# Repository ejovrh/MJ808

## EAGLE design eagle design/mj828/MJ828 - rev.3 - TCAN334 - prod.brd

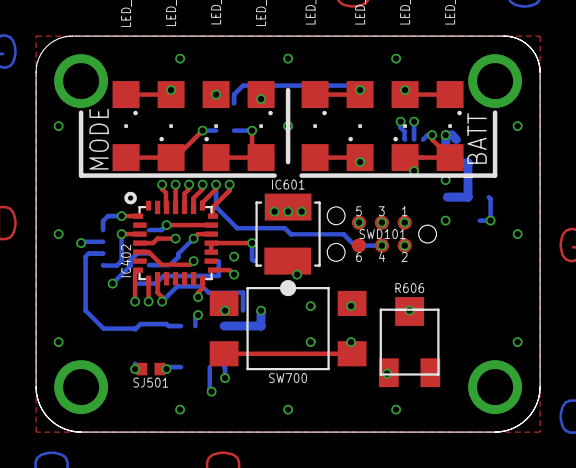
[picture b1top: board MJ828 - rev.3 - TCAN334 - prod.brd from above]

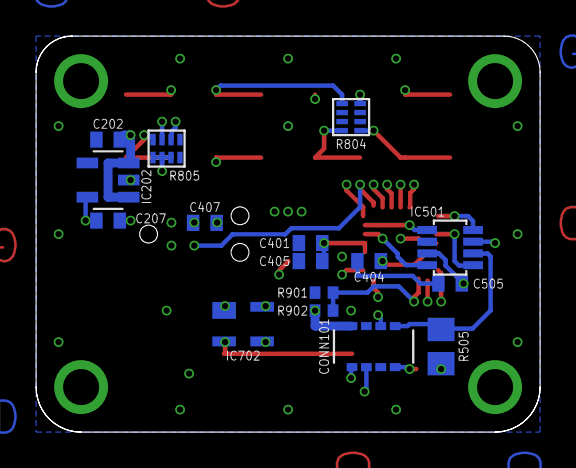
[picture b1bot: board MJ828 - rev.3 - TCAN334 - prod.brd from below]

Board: 4 copper layers, 28.0 x 22.0 mm, 30 parts (16 on the bottom side), 28 nets.

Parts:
C202: 1μF / 10V; C0402
C207: 1μF; C0402
C401, C405, C407: 0.1u; C0402
C404: 1u; C0402
C505: 0.1μF; C0402
CONN101: 104250-0820; SMD
IC202: LDK320AM33R; SOT-23-5L
IC402: STM32F042G6U6; UFQFPN-28
IC501: TCAN334; SOT23-8
IC601: SFH 320 FA-Z; P-LCC-2
IC702: MAX6816EUS+T; 4SOT143
LED_BATT801, LED_BATT802, LED_BATT803, LED_BATT804: 156120BS82500; SML1206
LED_BLUE800: 156120BS82500; SML1206
LED_GREEN800: 156120VS82500; SML1206
LED_RED800: 156120RS82500; SML1206
LED_YELLOW800: 156120YS82500; SML1206
R505: 120; R0805
R606: 3313J-1-104E - 100k; 3313
R804: 741X083151JP / 150Ω; 0402
R805: 741X083101JP / 100Ω; 0402
R901, R902: 100k; R0402
SJ501: CAN termination; R0402
SW700: TL3305CF160QG; SMD
SWD101: TC2030-NL

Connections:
3V3: C207.2, C401.2, C404.2, C405.2, C505.1, CONN101.P$7, IC202.OUT, IC402.5_VDDA, IC402.17_VDD, IC402.18_VDDIO2, IC501.P$3, IC702.4_VCC, R606.2_WIPER, SWD101.1_TVCC
!SHDN!: IC402.3_PF1, IC501.P$5
!STBY!: IC402.1_PB8, IC501.P$8
BAT+: C202.1, CONN101.P$5, IC202.EN, IC202.IN, R902.2
BREAK_IN: CONN101.P$4, IC402.8_PA2
CAN_H: CONN101.P$1, IC501.P$7, SJ501.2
CAN_INFRA:CAN_JMPR: R505.2, SJ501.1
CAN_L: CONN101.P$8, IC501.P$6, R505.1
CAN_RX: IC402.19_PA9-[PA11], IC501.P$4
CAN_TX: IC402.20_PA10-[PA12], IC501.P$1
CP1: IC402.26_PB5, LED_BATT803.A, LED_BATT804.C, LED_GREEN800.A, LED_RED800.C
CP2: IC402.24_PB3, LED_BLUE800.A, LED_YELLOW800.C, R804.8
CP3: IC402.25_PB4, LED_BATT801.C, LED_BATT802.A, R804.2
CP4: IC402.23_PA15, R805.2, R805.4, R805.6
GND: C202.2, C207.1, C401.1, C404.1, C405.1, C407.1, C505.2, CONN101.P$2, IC202.GND, IC402.16_VSS, IC501.P$2, IC601.EMITTER, IC702.1_GND, R901.1, SW700.3, SW700.4, SWD101.5_GND
HIGH_IN: CONN101.P$3, IC402.7_PA1
LED:D_BATT1&2: LED_BATT801.A, LED_BATT802.C, R805.3
LED:D_BATT3&4: LED_BATT803.C, LED_BATT804.A, R805.1
LED:D_BLUE: LED_BLUE800.C, R805.5
LED:D_RED&GREEN: LED_GREEN800.C, LED_RED800.A, R804.7
LED:D_YELLOW: LED_YELLOW800.A, R804.1
PHOTOTRANSISTOR: IC402.15_PB1, IC601.COLLECTOR, R606.3_CW
PUSHBUTTON:SWITCH_IN: IC702.2_IN, SW700.1, SW700.2
SWITCH: IC402.14_PB0, IC702.3_OUT
SYS_NRST: C407.2, IC402.4_NRST, SWD101.3_T_NRST
SYS_SWCLK: IC402.22_PA14, SWD101.4_T_SWCLK
SYS_SWDIO: IC402.21_PA13, SWD101.2_T_SWDIO
VBAT+: IC402.9_PA3, R901.2, R902.1

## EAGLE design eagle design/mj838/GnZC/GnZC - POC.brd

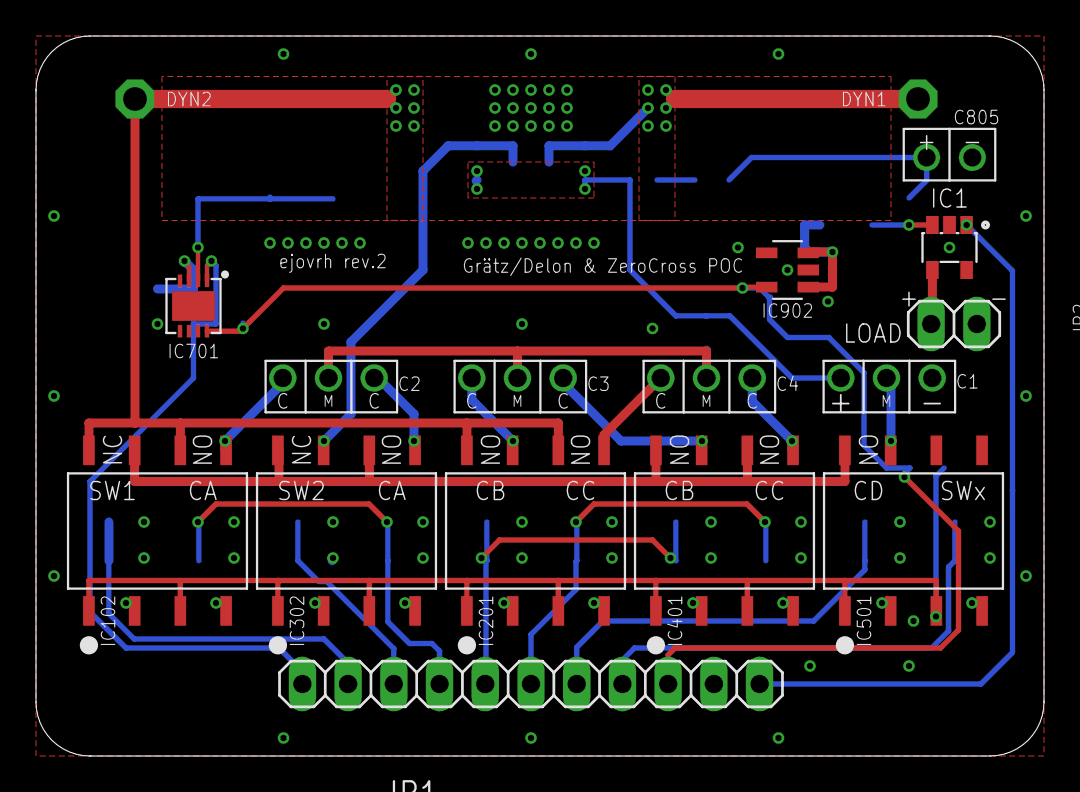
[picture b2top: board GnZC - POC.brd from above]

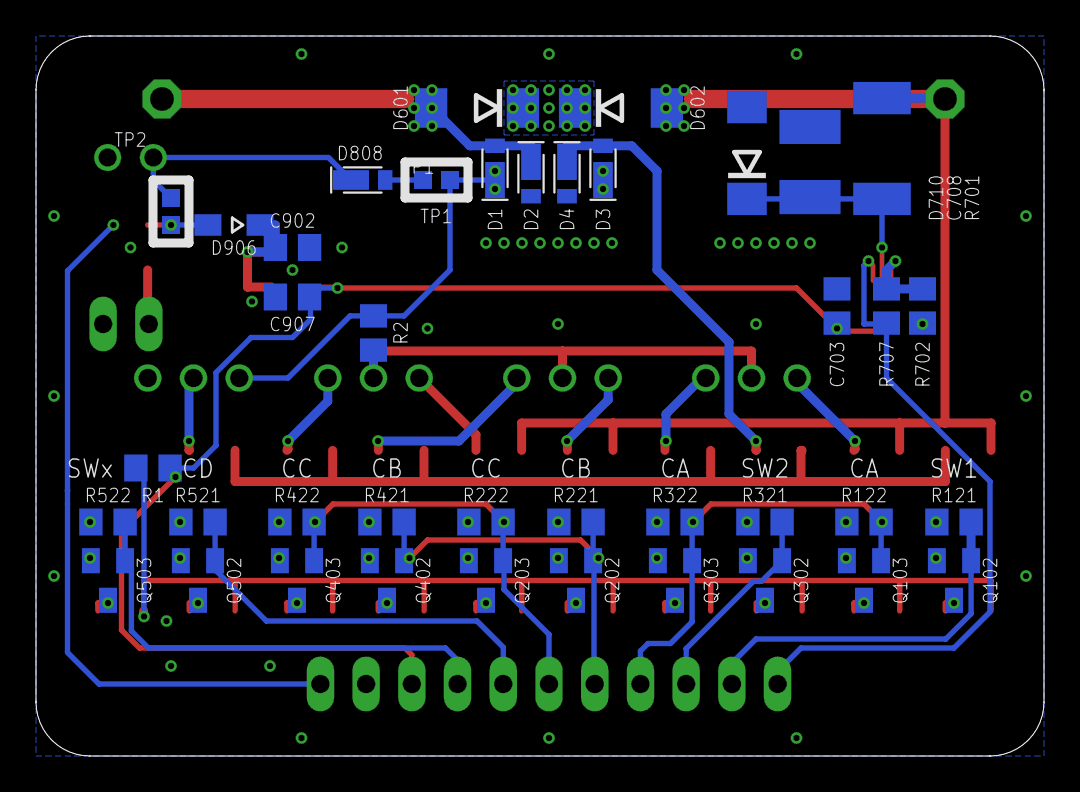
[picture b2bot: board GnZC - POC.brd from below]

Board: 2 copper layers, 56.0 x 40.0 mm, 59 parts (42 on the bottom side), 43 nets.

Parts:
C1: 330μF / 35V / ultralow ESR; TH-2S
C2, C3, C4: 1500μF / 35V / ultralow ESR; TH-2S-BACK-TO-BACK
C703: 0.1uF / 10V; C0805
C708: 10nF / 100v; C1812
C805: 2P 4700μF / 35V / ultralow ESR; TH
C902, C907: 1uF / 10V; C0805
D1, D2, D3, D4, D808: CUHS20S30,H3F; US2H
D601, D602: 19V/5W; DO214AA
D710: 6V/3W; DO214AA
D906: BAT 60A E6327; SOD323-W
IC1: MIC2514YM5; SOT-23-5
IC102, IC302: LBA710S; SMD_DIP8
IC201, IC401, IC501: LAA710S; SMD_DIP8
IC701: LT1638IDD#PBF; DFN-8
IC902: LDK320AM33R; SOT-23-5L
JP1: out; 1X11
JP2: 2.54-pinhead; 1X02
Q102, Q103, Q202, Q203, Q302, Q303, Q402, Q403, Q502, Q503: IRLML2402TRPBF; SOT23
R1: 430R/0.5W; R0805
R2: 47k; R0805
R121, R122, R221, R222, R321, R322, R421, R422, R521, R522, R702, R707: 10k; R0805
R701: 10k/3W; R2512
TP2: dynamo 1; P1-13
TP3: dynamo 2; P1-13
TP4: TP1l; TP10SQ
TP5: TP1r; TP10SQ
TP6: TP2l; TP10SQ
TP7: TP2r; TP10SQ

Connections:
3V3: C703.2, C907.2, IC701.8_V+, IC902.OUT, JP1.9, R1.2
3V3:LDK_IN: C902.1, D906.C, IC902.EN, IC902.IN
CAA: C2.1_C, IC102.5_DRAIN2-1
CAB: C2.3_C, IC302.5_DRAIN2-1
CBA: C3.1_C, IC201.7_DRAIN1-1
CBB: C3.3_C, IC401.7_DRAIN1-1
CCA: C4.1_C, IC201.5_DRAIN2-1
CCB: C4.3_C, IC401.5_DRAIN2-1
DYNAMO1: D1.C, D2.A, D601.A, TP2.TP
DYNAMO2_AFTER_TUNING-CAP_SW: IC102.7_DRAIN1-1, IC302.6_DRAIN2-2, IC302.8_DRAIN1-2, IC401.6_DRAIN2-2, IC401.8_DRAIN1-2, IC501.8_DRAIN1-2
DYNAMO2_BEFORE_TUNING-CAP_SW: D602.A, IC102.6_DRAIN2-2, IC102.8_DRAIN1-2, IC201.6_DRAIN2-2, IC201.8_DRAIN1-2, R701.1, TP3.TP
DYNAMO2_DELON: C1.2_MID, IC501.7_DRAIN1-1
DYNAMO2_GRAETZ: D3.C, D4.A, IC302.7_DRAIN1-1
GND: C1.3_NEG, C703.1, C708.1, C805.NEG, C902.2, C907.1, D2.C, D4.C, D710.A, IC1.P$2, IC701.4_V-, IC701.9_V-, IC902.GND, JP1.10, JP2.2, Q102.2, Q103.2, Q202.2, Q203.2, Q302.2, Q303.2, Q402.2, Q403.2, Q502.2, Q503.2, R121.2, R122.2, R221.2, R222.2, R321.2, R322.2, R421.2, R422.2, R521.2, R522.2, R702.1
LOAD_HIGHSIDE: IC1.P$4, JP2.1
LOAD_SWITCH: IC1.P$1, JP1.11
OVP:ZENER_COMMON: D601.C, D602.C
SSR_ANODE: IC102.1_ANODE1, IC102.3_ANODE2, IC201.1_ANODE1, IC201.3_ANODE2, IC302.1_ANODE1, IC302.3_ANODE2, IC401.1_ANODE1, IC401.3_ANODE2, IC501.1_ANODE1, IC501.3_ANODE2, R1.1
SSR_NC/NO1:SW1_CAT: IC102.2_CATHODE1, Q102.3
SSR_NC/NO1:SW2_CAT: IC102.4_CATHODE2, Q103.3
SSR_NC/NO2:SW1_CAT: IC302.2_CATHODE1, Q302.3
SSR_NC/NO2:SW2_CAT: IC302.4_CATHODE2, Q303.3
SSR_NO/NO1:SW1_CAT: IC201.2_CATHODE1, Q202.3
SSR_NO/NO1:SW2_CAT: IC201.4_CATHODE2, Q203.3
SSR_NO/NO2:SW1_CAT: IC401.2_CATHODE1, Q402.3
SSR_NO/NO2:SW2_CAT: IC401.4_CATHODE2, Q403.3
SSR_NO/NO3:SW1_CAT: IC501.2_CATHODE1, Q502.3
SSR_NO/NO3:SW2_CAT: IC501.4_CATHODE2, Q503.3
SW1_CTRL: JP1.2, Q102.1, R121.1
SW2_CTRL: JP1.3, Q302.1, R321.1
SW_CA_CTRL: JP1.4, Q103.1, Q303.1, R122.1, R322.1
SW_CB_CTRL: JP1.5, Q202.1, Q402.1, R221.1, R421.1
SW_CC_CTRL: JP1.6, Q203.1, Q403.1, R222.1, R422.1
SW_CD_CTRL: JP1.7, Q502.1, R521.1
SW_X_CTRL: JP1.8, Q503.1, R522.1
TUNING_CAP_BIAS: C2.2_MID, C3.2_MID, C4.2_MID, R2.1
V_RECT_TP1-IN: C1.1_POS, D1.A, D3.A, R2.2, TP4.TP
V_RECT_TP1-OUT: D808.C, TP5.TP
V_REGULATED_TP2-IN: C805.POS, D808.A, TP6.TP
V_REGULATED_TP2-OUT: D906.A, IC1.P$3, TP7.TP
ZERO-CROSS_DETECTOR:N$6: C708.2, D710.C, IC701.2_A_IN-, R701.2
ZERO-CROSS_DETECTOR:N$12: IC701.3_A_IN+, R702.2, R707.2
ZEROCROSS: IC701.1_A_OUT, JP1.1, R707.1

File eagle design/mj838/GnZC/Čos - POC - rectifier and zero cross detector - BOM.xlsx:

Qty | Value | Device | Package | Parts | mouser part no. | mouser url
1 | 0.1u | C-EUC0805 | C0805 | C703 | 80-C1812C104JDR | https://hr.mouser.com/ProductDetail/80-C1812C104JDR
12 | 10k | R-EU_R0805 | R0805 | R121 R122 R221 R222 R321 R322 R421 R422 R521 R522 R702 R707
1 | 10k/3W | R-EU_R2512 | R2512 | R701 | 652-CHP2512JW103ELF | https://hr.mouser.com/ProductDetail/652-CHP2512JW103ELF
1 | 10n/100v | C-EUC1812 | C1812 | C708 | 77-VJ1812Y103JXEAT | https://hr.mouser.com/ProductDetail/77-VJ1812Y103JXEAT
2 | 19V/5W | ZENER-DIODEDO214AA | DO214AA | D601 D602 | 833-SMBJ5356B-TP | https://hr.mouser.com/ProductDetail/833-SMBJ5356B-TP
2 | 1u / 10V | C-EUC0805 | C0805 | C902 C907 | 581-08051C105K4T2A | https://hr.mouser.com/ProductDetail/581-08051C105K4T2A
1 | 430R/0.5W | R-EU_R0805 | R0805 | R1 | 667-ERJ-P06F4300V | https://hr.mouser.com/ProductDetail/667-ERJ-P06F4300V
1 | 47k | R-EU_R0805 | R0805 | R2
1 | 6V/3W | ZENER-DIODEDO214AA | DO214AA | D710 | 494-SMBJ5340BE3/TR13 | https://hr.mouser.com/ProductDetail/494-SMBJ5340BE3-TR13
5 | CUHS20S30 H3F | CUHS20S30 | US2H | D1 D2 D3 D4 D808 | 757-CUHS20S30H3F | https://hr.mouser.com/ProductDetail/Toshiba/CUHS20S30H3F?qs=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
10 | IRLML2402TRPBF | MOSFET-NREFLOW | SOT23 | Q102 Q103 Q202 Q203 Q302 Q303 Q402 Q403 Q502 Q503 | 942-IRLML2402TRPBF | https://hr.mouser.com/ProductDetail/942-IRLML2402TRPBF
3 | LAA710S | LAA710 | SMD_DIP8 | IC201 IC401 IC501 | 849-LAA710S | https://hr.mouser.com/ProductDetail/849-LAA710S
2 | LBA710S | LBA710 | SMD_DIP8 | IC102 IC302 | 849-LBA710S | https://hr.mouser.com/ProductDetail/849-LBA710S
1 | LDK320AM33R | LDK320SOT-23-5L | SOT-23-5L | IC902 | 511-LDK320AM33R | https://hr.mouser.com/ProductDetail/511-LDK320AM33R
1 | LT1638IDD#PBF | LT1638 | DFN-8 | IC701 | 584-LT1638IDD#PBF | https://hr.mouser.com/ProductDetail/584-LT1638IDD%23PBF

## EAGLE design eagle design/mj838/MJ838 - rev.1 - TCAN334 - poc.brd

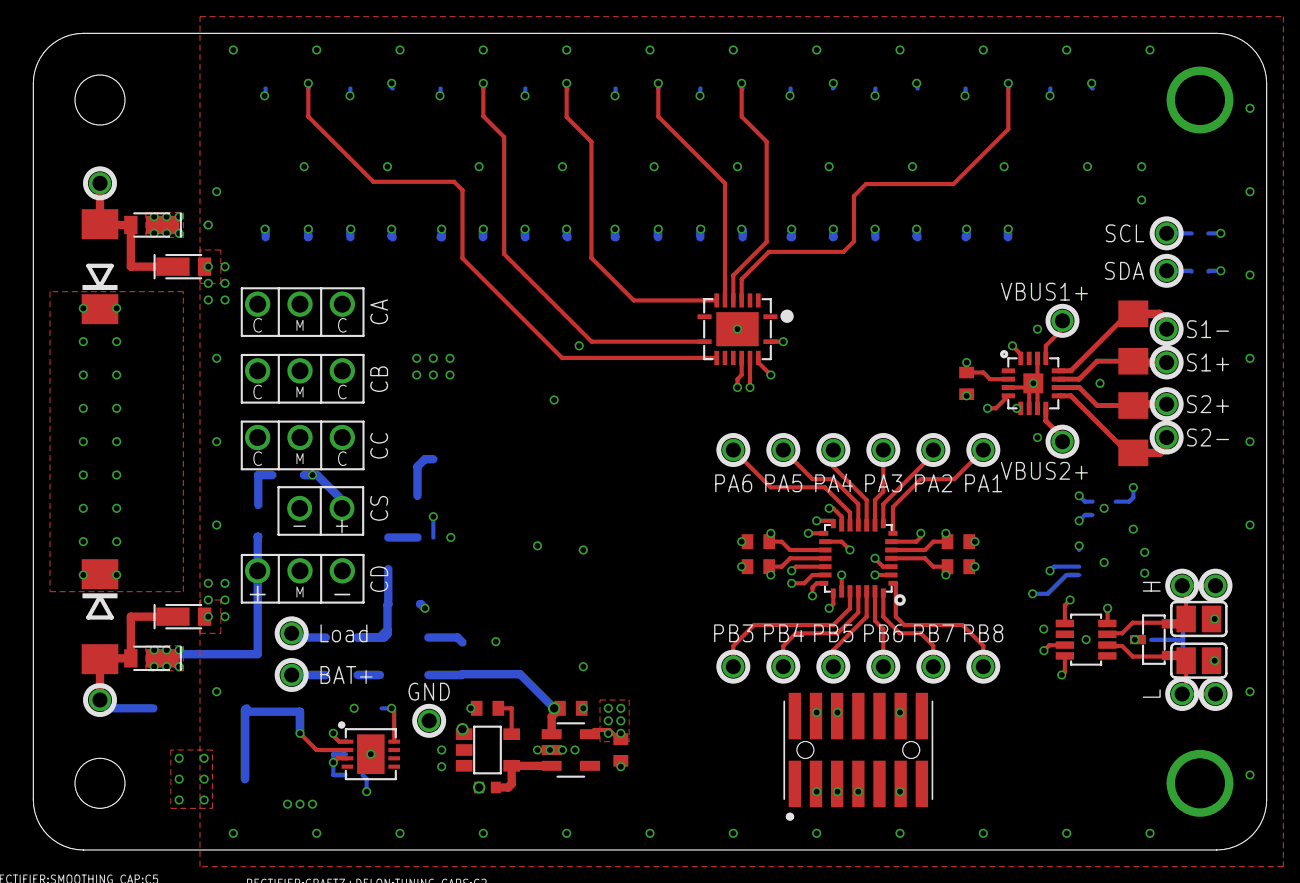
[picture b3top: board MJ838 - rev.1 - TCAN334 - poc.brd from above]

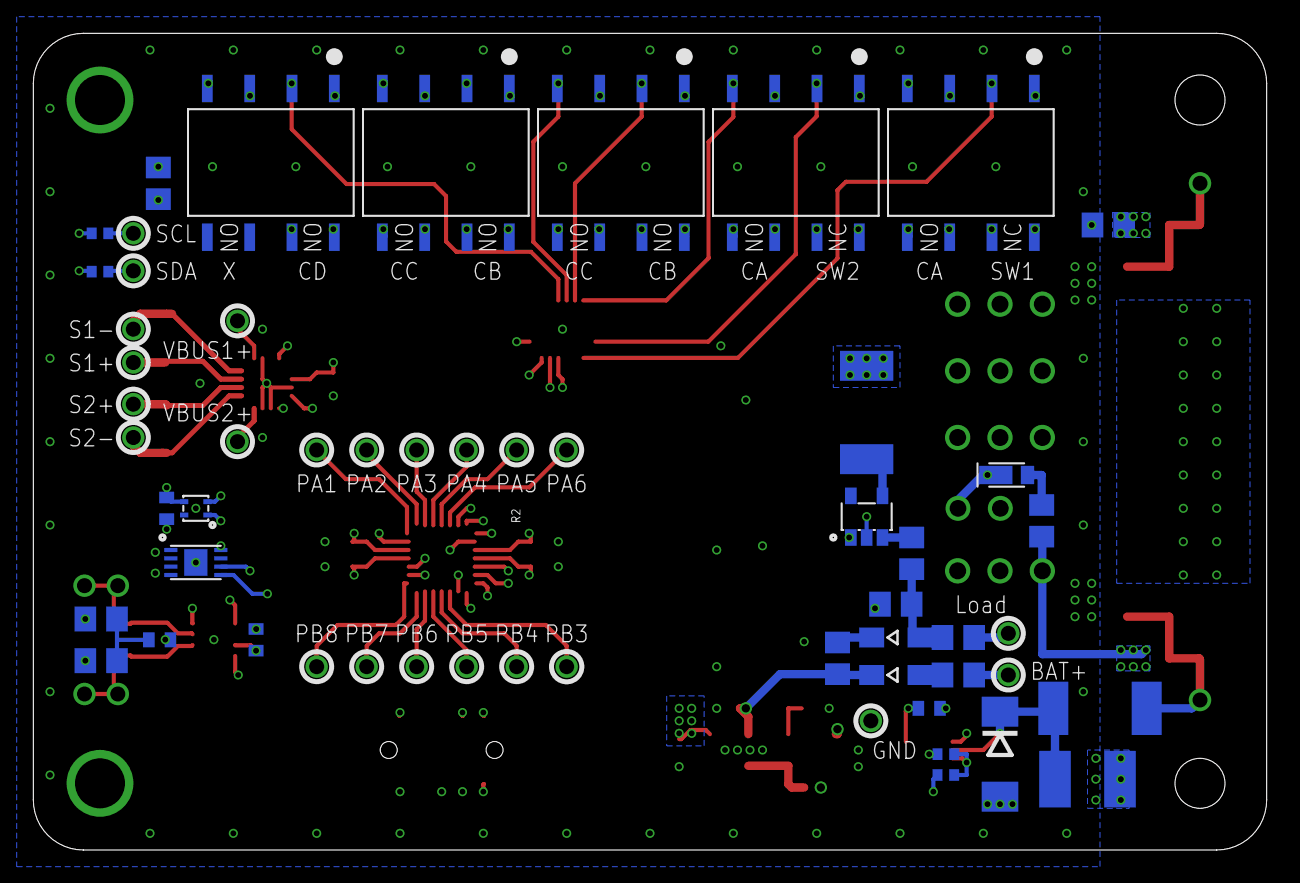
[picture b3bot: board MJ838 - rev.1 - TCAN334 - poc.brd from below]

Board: 6 copper layers, 74.0 x 49.0 mm, 95 parts (33 on the bottom side), 71 nets.

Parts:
C301, C305, C307, C405, C605, C905: 0.1uF / 10V; C0402
C304: 1uF / 10V; C0402
C401: 47nF / 10V; C0402
D501, D502: BAT 60A E6327; SOD323-W
IC302: STM32F042G6U6; UFQFPN-28
IC401: TCAN334GDCNT; SOT23-8
IC402: SZNUP2105LT1G; SOT-23-3
IC601: PAC1952T-1E/4MX; VQFN16
IC701: MB85RC16PN-G-AMERE1; SON-8
IC801: MIC2514YM5; SOT-23-5
IC901: SHT40-AD1F-R2; SMD
J1: FTSH-107-01-L-DV-K-A; FTSH10701LDVKA
R1, R2, R3, R502, R504, R505: 0R; R0805
R4, R5: 4k7; R0402
R401, R402: 60R, 0.5W; R0805
R601, R602: 0.1R / 0.5W / 0.25%; R1206
R802: 12R / 5W; R2512
RECTIFIER:3V3:C1, RECTIFIER:3V3:C2, RECTIFIER:3V3:C7: 1uF / 10V; C0402
RECTIFIER:3V3:IC1: R3119N058A; SOT23-5
RECTIFIER:3V3:IC2: LDK320AM33R; SOT-23-5L
RECTIFIER:3V3:R1: 100k / 0.1W; R0402
RECTIFIER:GRAETZ+DELON:D1, RECTIFIER:GRAETZ+DELON:D2, RECTIFIER:GRAETZ+DELON:D3, RECTIFIER:GRAETZ+DELON:D4: CUHS20S30,H3F; US2H
RECTIFIER:GRAETZ+DELON:DELON:C1: 330μF / 35V / ultralow ESR; TH-2S
RECTIFIER:GRAETZ+DELON:DELON:SSR_NO/NO3:IC1: LAA710S; SMD_DIP8
RECTIFIER:GRAETZ+DELON:IC1: TLC59208FIRGYR; VQFN16
RECTIFIER:GRAETZ+DELON:R1: 430R/0.5W; R0805
RECTIFIER:GRAETZ+DELON:TUNING_CAPS:C2, RECTIFIER:GRAETZ+DELON:TUNING_CAPS:C3, RECTIFIER:GRAETZ+DELON:TUNING_CAPS:C4: 1500μF / 35V / ultralow ESR; TH-2S-BACK-TO-BACK
RECTIFIER:GRAETZ+DELON:TUNING_CAPS:R2: 47k; R0805
RECTIFIER:GRAETZ+DELON:TUNING_CAPS:SSR_NC/NO1:IC2, RECTIFIER:GRAETZ+DELON:TUNING_CAPS:SSR_NC/NO2:IC2: LBA710S; SMD_DIP8
RECTIFIER:GRAETZ+DELON:TUNING_CAPS:SSR_NO/NO1:IC1, RECTIFIER:GRAETZ+DELON:TUNING_CAPS:SSR_NO/NO2:IC1: LAA710S; SMD_DIP8
RECTIFIER:OVP:D1, RECTIFIER:OVP:D2: 19V/5W; DO214AA
RECTIFIER:SMOOTHING_CAP:C5: 2P 4700μF / 35V / ultralow ESR; TH
RECTIFIER:SMOOTHING_CAP:D8: CUHS20S30,H3F; US2H
RECTIFIER:ZERO-CROSS_DETECTOR:C3: 0.1uF / 10V; C0402
RECTIFIER:ZERO-CROSS_DETECTOR:C8: 10nF / 100v; C1812
RECTIFIER:ZERO-CROSS_DETECTOR:D10: 6V/3W; DO214AA
RECTIFIER:ZERO-CROSS_DETECTOR:IC1: LT1638IDD#PBF; DFN-8
RECTIFIER:ZERO-CROSS_DETECTOR:R1: 10k/3W; R2512
RECTIFIER:ZERO-CROSS_DETECTOR:R2, RECTIFIER:ZERO-CROSS_DETECTOR:R7: 10k; R0402
SJ401: CAN H term.; SJ
SJ402: CAN L term.; SJ
TP1: BAT+; TH-0.9
TP2, TP3, TP4, TP5, TP6, TP7, TP8, TP9, TP10, TP11, TP12, TP13, TP14, TP15, TP16, TP17, TP21, TP22, TP23, TP24, TP25, TP26, TP27, TP28, TP29: CAN high; TH-0.9
TP18, TP19: CAN low; TH-0.9
TP20: GND; TH-0.9

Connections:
3V3: C301.2, C304.2, C305.2, C405.1, C605.1, C905.1, IC302.5_VDDA, IC302.17_VDD, IC302.18_VDDIO2, IC401.P$3, IC601.2_VDD, IC701.P$8, IC901.VDD, J1.3, R4.2, R5.2, RECTIFIER:3V3:C7.2, RECTIFIER:3V3:IC2.OUT, RECTIFIER:GRAETZ+DELON:IC1.16, RECTIFIER:GRAETZ+DELON:R1.2, RECTIFIER:ZERO-CROSS_DETECTOR:C3.2, RECTIFIER:ZERO-CROSS_DETECTOR:IC1.8_V+
!ARTIFICIAL_LOAD!: IC302.15_PB1, IC801.P$1
!LED_RST!: IC302.13_PA7, RECTIFIER:GRAETZ+DELON:IC1.13
!STBY!: IC302.23_PA15, IC401.P$8
ARTIFICIAL_LOAD:LOAD_HIGHSIDE: IC801.P$4, R802.2
ART_LOAD_IN: IC801.P$3, R2.2
BAT: D501.A, R1.1
BAT+: R1.2, TP1.P$1
CAN_H: IC401.P$7, IC402.2, SJ401.1, TP16.P$1, TP17.P$1
CAN_INFRA:H: R402.2, SJ401.2
CAN_INFRA:L: R401.1, SJ402.2
CAN_INFRA:SPLIT: C401.1, R401.2, R402.1
CAN_L: IC401.P$6, IC402.1, SJ402.1, TP18.P$1, TP19.P$1
CAN_RX: IC302.19_PA9-[PA11], IC401.P$4
CAN_TX: IC302.20_PA10-[PA12], IC401.P$1
DYNAMO1: RECTIFIER:GRAETZ+DELON:D1.C, RECTIFIER:GRAETZ+DELON:D2.A, RECTIFIER:GRAETZ+DELON:TUNING_CAPS:SSR_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.6_DRAIN2-2, RECTIFIER:GRAETZ+DELON:TUNING_CAPS:SSR_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.8_DRAIN1-2, RECTIFIER:GRAETZ+DELON:TUNING_CAPS:SSR_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.6_DRAIN2-2, RECTIFIER:GRAETZ+DELON:TUNING_CAPS:SSR_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.8_DRAIN1-2, RECTIFIER:OVP:D1.A, TP2.P$1
DYNAMO2: RECTIFIER:GRAETZ+DELON:D3.C, RECTIFIER:GRAETZ+DELON:D4.A, RECTIFIER:GRAETZ+DELON:TUNING_CAPS:SSR_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.7_DRAIN1-1, RECTIFIER:OVP:D2.A, RECTIFIER:ZERO-CROSS_DETECTOR:R1.1, TP3.P$1
GND: C301.1, C304.1, C305.1, C307.1, C401.2, C405.2, C605.2, C905.2, IC302.16_VSS, IC401.P$2, IC402.3, IC601.3_GND, IC601.6_ADDRSEL, IC601.7_VBUS2-, IC601.14_VBUS1-, IC601.17_GND, IC701.P$1, IC701.P$2, IC701.P$3, IC701.P$4, IC701.P$9, IC801.P$2, IC901.VSS, J1.5, J1.7, J1.11, R802.1, RECTIFIER:3V3:C1.2, RECTIFIER:3V3:C2.2, RECTIFIER:3V3:C7.1, RECTIFIER:3V3:IC1.2_GND, RECTIFIER:3V3:IC1.3_GND, RECTIFIER:3V3:IC2.GND, RECTIFIER:GRAETZ+DELON:D2.C, RECTIFIER:GRAETZ+DELON:D4.C, RECTIFIER:GRAETZ+DELON:DELON:C1.3_NEG, RECTIFIER:GRAETZ+DELON:IC1.1, RECTIFIER:GRAETZ+DELON:IC1.2, RECTIFIER:GRAETZ+DELON:IC1.3, RECTIFIER:GRAETZ+DELON:IC1.8, RECTIFIER:GRAETZ+DELON:IC1.17, RECTIFIER:SMOOTHING_CAP:C5.NEG, RECTIFIER:ZERO-CROSS_DETECTOR:C3.1, RECTIFIER:ZERO-CROSS_DETECTOR:C8.1, RECTIFIER:ZERO-CROSS_DETECTOR:D10.A, RECTIFIER:ZERO-CROSS_DETECTOR:IC1.4_V-, RECTIFIER:ZERO-CROSS_DETECTOR:IC1.9_V-, RECTIFIER:ZERO-CROSS_DETECTOR:R2.1, TP20.P$1
I2C_SCL: IC302.3_PF1, IC601.4_SCL, IC701.P$6, IC901.SCL, R4.1, RECTIFIER:GRAETZ+DELON:IC1.14, TP22.P$1
I2C_SDA: IC302.2_PF0, IC601.5_SDA, IC701.P$5, IC901.SDA, R5.1, RECTIFIER:GRAETZ+DELON:IC1.15, TP23.P$1
LOAD2: R3.1, TP21.P$1
PA1: IC302.7_PA1, TP4.P$1
PA2: IC302.8_PA2, TP5.P$1
PA3: IC302.9_PA3, TP6.P$1
PA4: IC302.10_PA4, TP7.P$1
PA5: IC302.11_PA5, TP8.P$1
PA6: IC302.12_PA6, TP9.P$1
PB3: IC302.24_PB3, TP10.P$1
PB4: IC302.25_PB4, TP11.P$1
PB5: IC302.26_PB5, TP12.P$1
PB6: IC302.27_PB6, TP13.P$1
PB7: IC302.28_PB7, TP14.P$1
PB8: IC302.1_PB8, TP15.P$1
PM_!PWRDN!: IC302.6_PA0, IC601.16_!PWRDN!
RECTIFIER:3V3:!EN!: RECTIFIER:3V3:IC1.4_DOUT, RECTIFIER:3V3:IC2.EN, RECTIFIER:3V3:R1.2
RECTIFIER:3V3:CD: RECTIFIER:3V3:C1.1, RECTIFIER:3V3:IC1.5_CD
RECTIFIER:GRAETZ+DELON:!SW1!: RECTIFIER:GRAETZ+DELON:IC1.10, RECTIFIER:GRAETZ+DELON:TUNING_CAPS:SSR_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.2_CATHODE1
RECTIFIER:GRAETZ+DELON:!SW2!: RECTIFIER:GRAETZ+DELON:IC1.9, RECTIFIER:GRAETZ+DELON:TUNING_CAPS:SSR_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.2_CATHODE1
RECTIFIER:GRAETZ+DELON:!SW_CA!: RECTIFIER:GRAETZ+DELON:IC1.7, RECTIFIER:GRAETZ+DELON:TUNING_CAPS:SSR_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.4_CATHODE2, RECTIFIER:GRAETZ+DELON:TUNING_CAPS:SSR_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.4_CATHODE2
RECTIFIER:GRAETZ+DELON:!SW_CB!: RECTIFIER:GRAETZ+DELON:IC1.6, RECTIFIER:GRAETZ+DELON:TUNING_CAPS:SSR_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.2_CATHODE1, RECTIFIER:GRAETZ+DELON:TUNING_CAPS:SSR_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.2_CATHODE1
RECTIFIER:GRAETZ+DELON:!SW_CC!: RECTIFIER:GRAETZ+DELON:IC1.5, RECTIFIER:GRAETZ+DELON:TUNING_CAPS:SSR_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.4_CATHODE2, RECTIFIER:GRAETZ+DELON:TUNING_CAPS:SSR_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.4_CATHODE2
RECTIFIER:GRAETZ+DELON:!SW_CD!: RECTIFIER:GRAETZ+DELON:DELON:SSR_NO/NO3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.2_CATHODE1, RECTIFIER:GRAETZ+DELON:IC1.4
RECTIFIER:GRAETZ+DELON:DELON: RECTIFIER:GRAETZ+DELON:DELON:SSR_NO/NO3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.8_DRAIN1-2, RECTIFIER:GRAETZ+DELON:TUNING_CAPS:SSR_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.7_DRAIN1-1, RECTIFIER:GRAETZ+DELON:TUNING_CAPS:SSR_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.6_DRAIN2-2, RECTIFIER:GRAETZ+DELON:TUNING_CAPS:SSR_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.8_DRAIN1-2, RECTIFIER:GRAETZ+DELON:TUNING_CAPS:SSR_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.6_DRAIN2-2, RECTIFIER:GRAETZ+DELON:TUNING_CAPS:SSR_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.8_DRAIN1-2
RECTIFIER:GRAETZ+DELON:DELON:SW1_OUT: RECTIFIER:GRAETZ+DELON:DELON:C1.2_MID, RECTIFIER:GRAETZ+DELON:DELON:SSR_NO/NO3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.7_DRAIN1-1
RECTIFIER:GRAETZ+DELON:SSR_ANODE: RECTIFIER:GRAETZ+DELON:DELON:SSR_NO/NO3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.1_ANODE1, RECTIFIER:GRAETZ+DELON:DELON:SSR_NO/NO3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.3_ANODE2, RECTIFIER:GRAETZ+DELON:R1.1, RECTIFIER:GRAETZ+DELON:TUNING_CAPS:SSR_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.1_ANODE1, RECTIFIER:GRAETZ+DELON:TUNING_CAPS:SSR_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.3_ANODE2, RECTIFIER:GRAETZ+DELON:TUNING_CAPS:SSR_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.1_ANODE1, RECTIFIER:GRAETZ+DELON:TUNING_CAPS:SSR_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.3_ANODE2, RECTIFIER:GRAETZ+DELON:TUNING_CAPS:SSR_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.1_ANODE1, RECTIFIER:GRAETZ+DELON:TUNING_CAPS:SSR_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.3_ANODE2, RECTIFIER:GRAETZ+DELON:TUNING_CAPS:SSR_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.1_ANODE1, RECTIFIER:GRAETZ+DELON:TUNING_CAPS:SSR_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.3_ANODE2
RECTIFIER:GRAETZ+DELON:TUNING_CAPS:CAA: RECTIFIER:GRAETZ+DELON:TUNING_CAPS:C2.1_C, RECTIFIER:GRAETZ+DELON:TUNING_CAPS:SSR_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.5_DRAIN2-1
RECTIFIER:GRAETZ+DELON:TUNING_CAPS:CAB: RECTIFIER:GRAETZ+DELON:TUNING_CAPS:C2.3_C, RECTIFIER:GRAETZ+DELON:TUNING_CAPS:SSR_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.5_DRAIN2-1
RECTIFIER:GRAETZ+DELON:TUNING_CAPS:CBA: RECTIFIER:GRAETZ+DELON:TUNING_CAPS:C3.1_C, RECTIFIER:GRAETZ+DELON:TUNING_CAPS:SSR_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.7_DRAIN1-1
RECTIFIER:GRAETZ+DELON:TUNING_CAPS:CBB: RECTIFIER:GRAETZ+DELON:TUNING_CAPS:C3.3_C, RECTIFIER:GRAETZ+DELON:TUNING_CAPS:SSR_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.7_DRAIN1-1
RECTIFIER:GRAETZ+DELON:TUNING_CAPS:CCA: RECTIFIER:GRAETZ+DELON:TUNING_CAPS:C4.1_C, RECTIFIER:GRAETZ+DELON:TUNING_CAPS:SSR_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.5_DRAIN2-1
RECTIFIER:GRAETZ+DELON:TUNING_CAPS:CCB: RECTIFIER:GRAETZ+DELON:TUNING_CAPS:C4.3_C, RECTIFIER:GRAETZ+DELON:TUNING_CAPS:SSR_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.5_DRAIN2-1
RECTIFIER:GRAETZ+DELON:TUNING_CAPS:TUNING_CAP_BIAS: RECTIFIER:GRAETZ+DELON:TUNING_CAPS:C2.2_MID, RECTIFIER:GRAETZ+DELON:TUNING_CAPS:C3.2_MID, RECTIFIER:GRAETZ+DELON:TUNING_CAPS:C4.2_MID, RECTIFIER:GRAETZ+DELON:TUNING_CAPS:R2.1
RECTIFIER:LDO_IN: D501.C, R504.2, RECTIFIER:3V3:C2.1, RECTIFIER:3V3:IC1.1_VDD, RECTIFIER:3V3:IC2.IN, RECTIFIER:3V3:R1.1
RECTIFIER:OVP:ZENER_COMMON: RECTIFIER:OVP:D1.C, RECTIFIER:OVP:D2.C
RECTIFIER:SMOOTHINGCAP_IN: R502.2, RECTIFIER:SMOOTHING_CAP:D8.C
RECTIFIER:SMOOTHINGCAP_OUT: R505.1, RECTIFIER:SMOOTHING_CAP:C5.POS, RECTIFIER:SMOOTHING_CAP:D8.A
RECTIFIER:VDC_TOWARDS_LDO: D502.C, R504.1
RECTIFIER:V_RECT_TP1-IN: R502.1, RECTIFIER:GRAETZ+DELON:D1.A, RECTIFIER:GRAETZ+DELON:D3.A, RECTIFIER:GRAETZ+DELON:DELON:C1.1_POS, RECTIFIER:GRAETZ+DELON:TUNING_CAPS:R2.2
RECTIFIER:ZERO-CROSS_DETECTOR:OPAMP_IN+: RECTIFIER:ZERO-CROSS_DETECTOR:IC1.3_A_IN+, RECTIFIER:ZERO-CROSS_DETECTOR:R2.2, RECTIFIER:ZERO-CROSS_DETECTOR:R7.2
RECTIFIER:ZERO-CROSS_DETECTOR:OPAMP_IN-: RECTIFIER:ZERO-CROSS_DETECTOR:C8.2, RECTIFIER:ZERO-CROSS_DETECTOR:D10.C, RECTIFIER:ZERO-CROSS_DETECTOR:IC1.2_A_IN-, RECTIFIER:ZERO-CROSS_DETECTOR:R1.2
SENSE1+: IC601.11_SENSE1+, R601.1, TP26.P$1
SENSE1-: IC601.12_SENSE1-, R601.2, TP27.P$1
SENSE2+: IC601.10_SENSE2+, R602.1, TP28.P$1
SENSE2-: IC601.9_SENSE2-, R602.2, TP29.P$1
SYS_NRST: C307.2, IC302.4_NRST, J1.12
SYS_SWCLK: IC302.22_PA14, J1.6
SYS_SWDIO: IC302.21_PA13, J1.4
VBUS1+: IC601.13_VBUS1+, TP24.P$1
VBUS2+: IC601.8_VBUS2+, TP25.P$1
VDC: D502.A, R2.1, R3.2, R505.2
ZEROCROSS: IC302.14_PB0, RECTIFIER:ZERO-CROSS_DETECTOR:IC1.1_A_OUT, RECTIFIER:ZERO-CROSS_DETECTOR:R7.1

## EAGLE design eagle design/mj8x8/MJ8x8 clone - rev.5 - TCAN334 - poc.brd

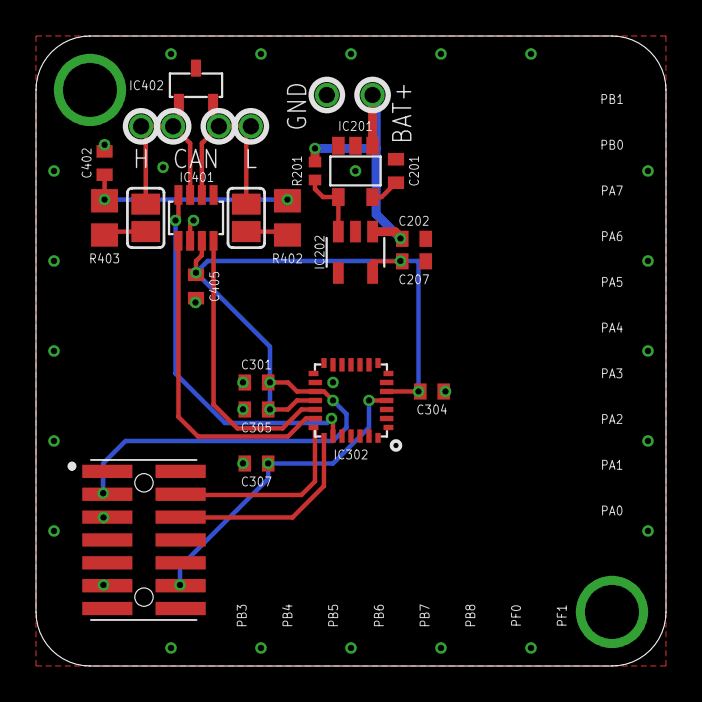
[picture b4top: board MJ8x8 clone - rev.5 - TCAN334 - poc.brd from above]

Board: 2 copper layers, 35.0 x 35.0 mm, 26 parts (0 on the bottom side), 16 nets.

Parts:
C201: 0.01uF / 10V; C0402
C202, C207, C304: 1uF / 10V; C0402
C301, C305, C307, C405: 0.1uF / 10V; C0402
C402: 47nF / 10V; C0402
IC201: R3119N058A-TR-FE; SOT23-5
IC202: LDK320AM33R; SOT-23-5L
IC302: STM32F042G6U6; UFQFPN-28
IC401: TCAN334; SOT23-8
IC402: SZNUP2105LT1G; SOT-23-3
J1: FTSH-107-01-L-DV-K-A; FTSH10701LDVKA
R201: 100k; R0402
R402, R403: 60R, 0.5W; R0805
SJ401: CAN H term.; SJ
SJ402: CAN L term.; SJ
TP1: LiIon + Terminal; TH-0.9
TP2: LiIon - Terminal; TH-0.9
TP5, TP6: CAN high; TH-0.9
TP7, TP8: CAN low; TH-0.9

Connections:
3V3: C207.2, C301.2, C304.2, C305.2, C405.1, IC202.OUT, IC302.5_VDDA, IC302.17_VDD, IC302.18_VDDIO2, IC401.P$3, J1.3
!STBY!: IC302.23_PA15, IC401.P$8
BAT+: C202.1, IC201.1_VDD, IC202.IN, R201.1, TP1.P$1
CAN_H: IC401.P$7, IC402.1, SJ401.1, TP5.P$1, TP6.P$1
CAN_INFRA:H: R403.2, SJ401.2
CAN_INFRA:L: R402.1, SJ402.2
CAN_INFRA:SPLIT: C402.1, R402.2, R403.1
CAN_L: IC401.P$6, IC402.2, SJ402.1, TP7.P$1, TP8.P$1
CAN_RX: IC302.19_PA9-[PA11], IC401.P$4
CAN_TX: IC302.20_PA10-[PA12], IC401.P$1
GND: C201.2, C202.2, C207.1, C301.1, C304.1, C305.1, C307.1, C402.2, C405.2, IC201.2_GND, IC201.3_GND, IC202.GND, IC302.16_VSS, IC401.P$2, IC402.3, J1.5, J1.7, J1.11, TP2.P$1
POWER_3V3:CD: C201.1, IC201.5_CD
POWER_3V3:EN: IC201.4_DOUT, IC202.EN, R201.2
SYS_NRST: C307.2, IC302.4_NRST, J1.12
SYS_SWCLK: IC302.22_PA14, J1.6
SYS_SWDIO: IC302.21_PA13, J1.4

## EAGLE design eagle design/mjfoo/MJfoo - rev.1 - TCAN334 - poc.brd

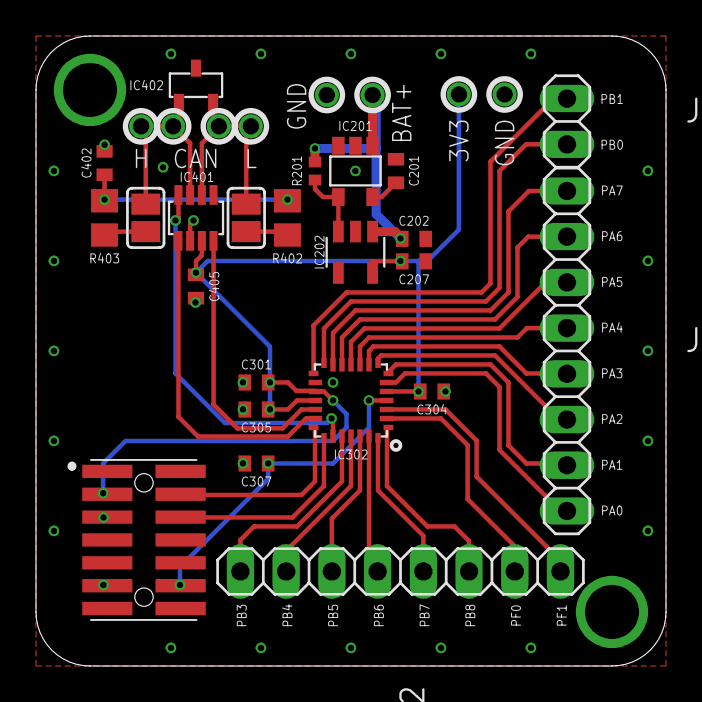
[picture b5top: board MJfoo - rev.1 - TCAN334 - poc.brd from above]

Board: 2 copper layers, 35.0 x 35.0 mm, 31 parts (0 on the bottom side), 34 nets.

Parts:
C201: 0.01uF / 10V; C0402
C202, C207, C304: 1uF / 10V; C0402
C301, C305, C307, C405: 0.1uF / 10V; C0402
C402: 47nF / 10V; C0402
IC201: R3119N058A-TR-FE; SOT23-5
IC202: LDK320AM33R; SOT-23-5L
IC302: STM32F042G6U6; UFQFPN-28
IC401: TCAN334; SOT23-8
IC402: SZNUP2105LT1G; SOT-23-3
J1: FTSH-107-01-L-DV-K-A; FTSH10701LDVKA
JP501: 1X02
JP502, JP503: 1X08
R201: 100k; R0402
R402, R403: 60R, 0.5W; R0805
SJ401: CAN H term.; SJ
SJ402: CAN L term.; SJ
TP1: LiIon + Terminal; TH-0.9
TP2, TP3, TP4: LiIon - Terminal; TH-0.9
TP5, TP6: CAN high; TH-0.9
TP7, TP8: CAN low; TH-0.9

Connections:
3V3: C207.2, C301.2, C304.2, C305.2, C405.1, IC202.OUT, IC302.5_VDDA, IC302.17_VDD, IC302.18_VDDIO2, IC401.P$3, J1.3, TP3.P$1
!STBY!: IC302.23_PA15, IC401.P$8
BAT+: C202.1, IC201.1_VDD, IC202.IN, R201.1, TP1.P$1
CAN_H: IC401.P$7, IC402.1, SJ401.1, TP5.P$1, TP6.P$1
CAN_INFRA:H: R403.2, SJ401.2
CAN_INFRA:L: R402.1, SJ402.2
CAN_INFRA:SPLIT: C402.1, R402.2, R403.1
CAN_L: IC401.P$6, IC402.2, SJ402.1, TP7.P$1, TP8.P$1
CAN_RX: IC302.19_PA9-[PA11], IC401.P$4
CAN_TX: IC302.20_PA10-[PA12], IC401.P$1
GND: C201.2, C202.2, C207.1, C301.1, C304.1, C305.1, C307.1, C402.2, C405.2, IC201.2_GND, IC201.3_GND, IC202.GND, IC302.16_VSS, IC401.P$2, IC402.3, J1.5, J1.7, J1.11, TP2.P$1, TP4.P$1
PA0: IC302.6_PA0, JP503.1
PA1: IC302.7_PA1, JP503.2
PA2: IC302.8_PA2, JP503.3
PA3: IC302.9_PA3, JP503.4
PA4: IC302.10_PA4, JP503.5
PA5: IC302.11_PA5, JP503.6
PA6: IC302.12_PA6, JP503.7
PA7: IC302.13_PA7, JP503.8
PB0: IC302.14_PB0, JP501.1
PB1: IC302.15_PB1, JP501.2
PB3: IC302.24_PB3, JP502.1
PB4: IC302.25_PB4, JP502.2
PB5: IC302.26_PB5, JP502.3
PB6: IC302.27_PB6, JP502.4
PB7: IC302.28_PB7, JP502.5
PB8: IC302.1_PB8, JP502.6
PF0: IC302.2_PF0, JP502.7
PF1: IC302.3_PF1, JP502.8
POWER_3V3:CD: C201.1, IC201.5_CD
POWER_3V3:EN: IC201.4_DOUT, IC202.EN, R201.2
SYS_NRST: C307.2, IC302.4_NRST, J1.12
SYS_SWCLK: IC302.22_PA14, J1.6
SYS_SWDIO: IC302.21_PA13, J1.4

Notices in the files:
parts and their libraries:
tag-connect: ©2009 ROFA.cz - modified and updated by Robert Darlington ‹rdarlington@gmail.com›
